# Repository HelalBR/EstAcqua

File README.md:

# EstAcqua
More details about implementation and code. Work in Progress. Check it out later.

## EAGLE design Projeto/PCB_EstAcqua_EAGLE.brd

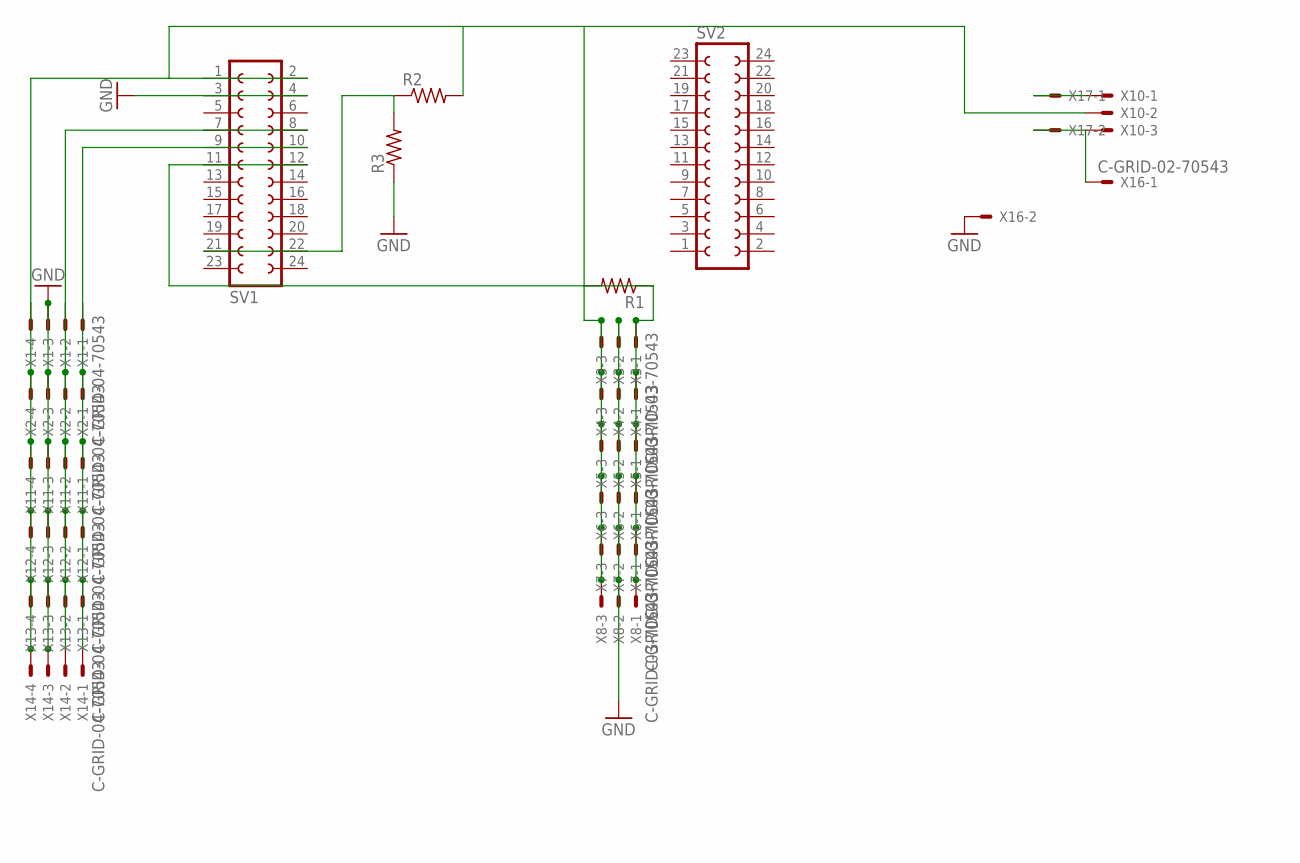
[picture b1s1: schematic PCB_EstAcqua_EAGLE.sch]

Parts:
R1: R-US_0207/15; 0207/15
R2, R3: R-US_0207/10; 0207/10
SV1, SV2: FE12-2W
X1, X2, X11, X12, X13, X14: C-GRID-04-70543; 70543-04
X3, X4, X5, X6, X7, X8: C-GRID-03-70543; 70543-03
X10: KK-156-3
X16: C-GRID-02-70543; 70543-02
X17: KK-156-2

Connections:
GND: R3.1, SV1.3, SV1.4, X1.3, X2.3, X3.2, X4.2, X5.2, X6.2, X7.2, X8.2, X11.3, X12.3, X13.3, X14.3, X16.2
unnamed: X10.1, X17.1
unnamed: R2.1, R3.2, SV1.21, SV1.22
unnamed: X10.3, X16.1, X17.2
unnamed: SV1.9, SV1.10, X1.1, X2.1, X11.1, X12.1, X13.1, X14.1
unnamed: R1.1, SV1.11, SV1.12, X3.1, X4.1, X5.1, X6.1, X7.1, X8.1
unnamed: SV1.7, SV1.8, X1.2, X2.2, X11.2, X12.2, X13.2, X14.2
VCC: R1.2, R2.2, SV1.1, SV1.2, X1.4, X2.4, X3.3, X4.3, X5.3, X6.3, X7.3, X8.3, X10.2, X11.4, X12.4, X13.4, X14.4

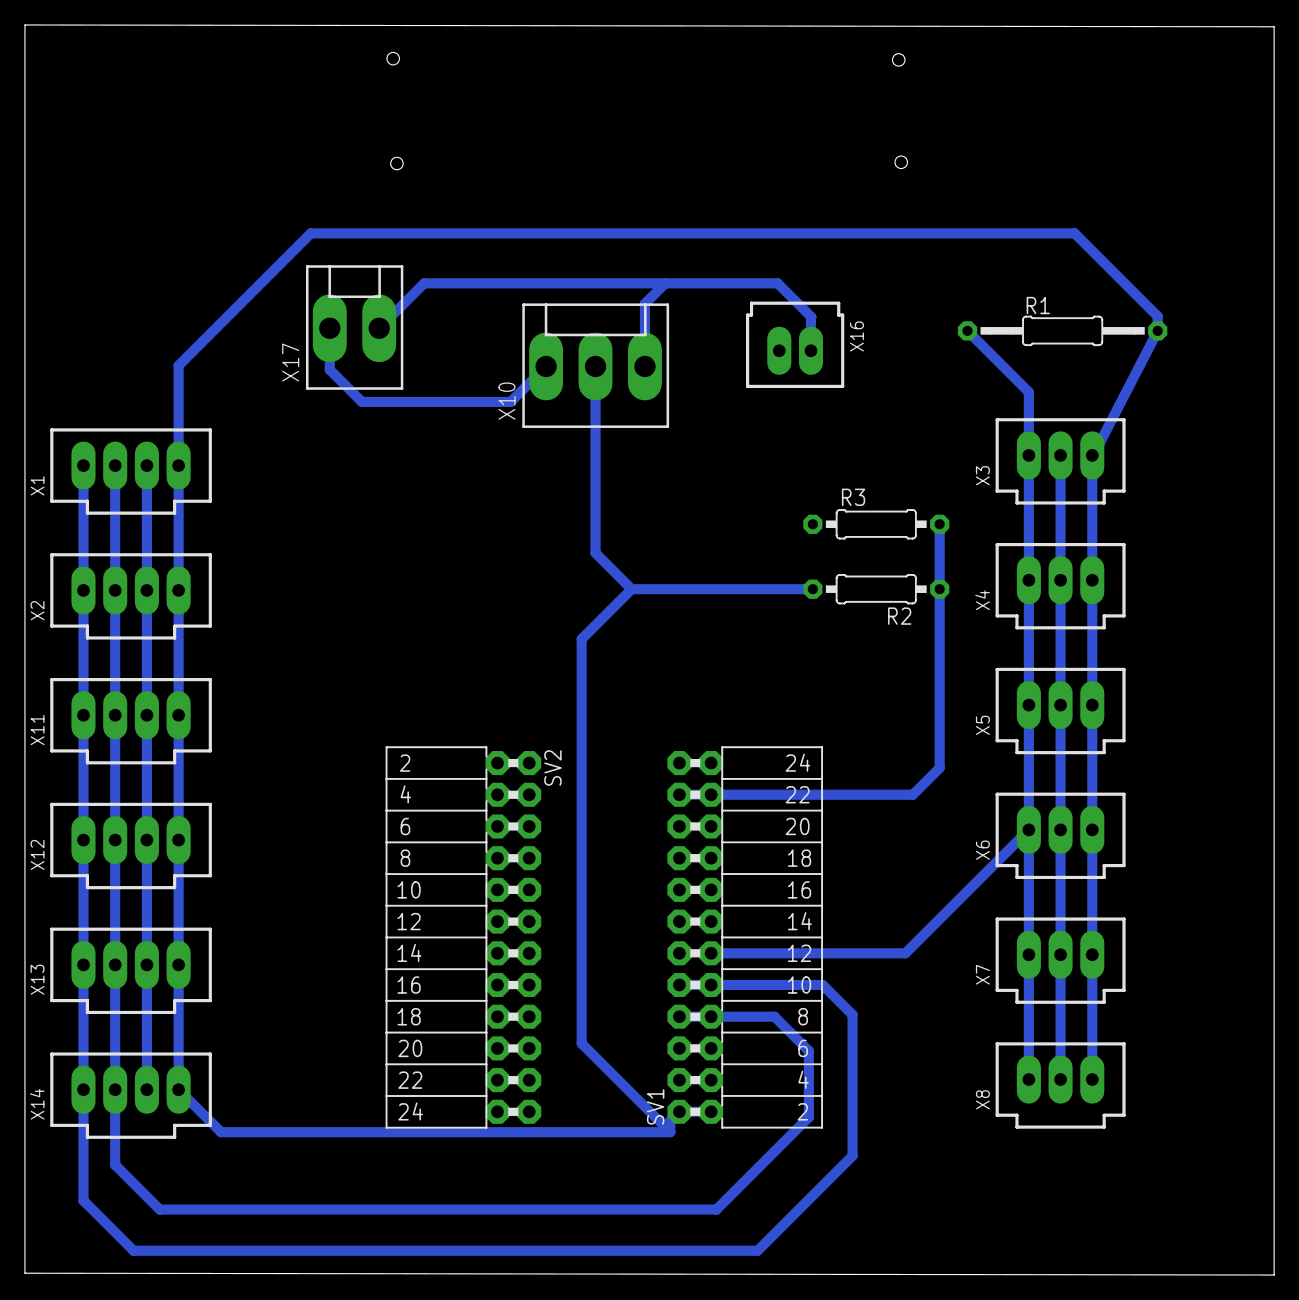
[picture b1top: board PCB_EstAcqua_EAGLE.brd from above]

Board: 2 copper layers, 100.1 x 100.1 mm, 20 parts (0 on the bottom side), 8 nets.

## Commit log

2019-02-16 Criação do Boot.py
2019-02-16 Criação do config.py
2019-02-16 Criação do main.py
2019-02-16 Rename nano gateway.py to nanogateway.py
2019-02-17 Add files via upload
    Datasheets de equipamentos usados na EstAcqua (durante a produção e no produto final)
2019-02-17 Add files via upload
    Artigos e documentos sobre LoRaWAN, calibração de sensores e colisão de pacotes
2019-02-17 Add files via upload
    PCB projetada para o nó. Priorizando a redução do consumo de energia.
2019-02-17 Add files via upload
    Dissertação de Mestrado defendida na Universidade Federal do Espírito Santo (UFES) com o projeto da EstAcqua
